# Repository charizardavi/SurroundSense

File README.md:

## SurroundSense by Haptify

Hardware:
- Dual-core XTensa LX7 MCU (ESP32-S3)
- Wifi and BLE capability
- On-board microphone
- Advanced haptic motor driver (DRV2605)

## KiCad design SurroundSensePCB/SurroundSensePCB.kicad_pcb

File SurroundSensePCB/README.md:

## SurroundSense by Haptify

Hardware:
- Dual-core XTensa LX7 MCU (ESP32-S3)
- Wifi and BLE capability
- On-board microphone
- Advanced haptic motor driver (DRV2605)

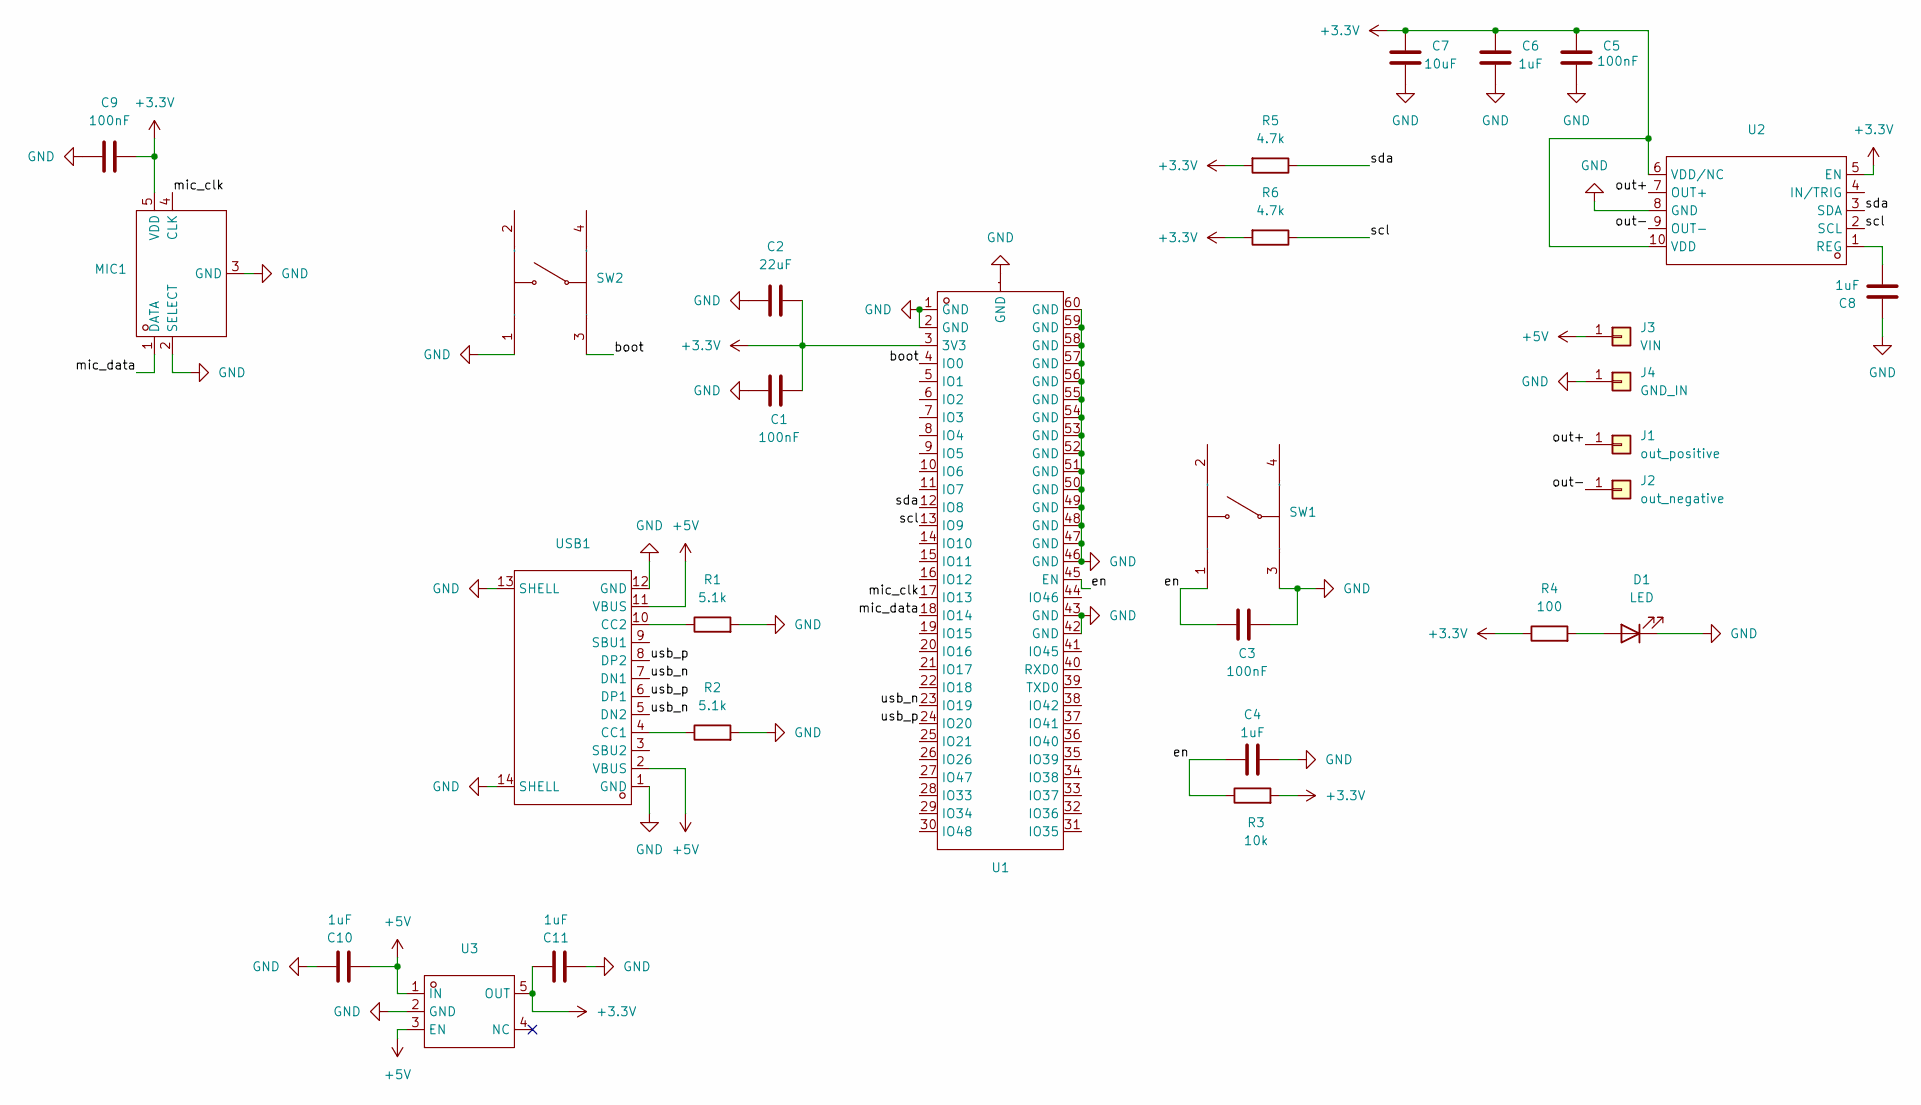
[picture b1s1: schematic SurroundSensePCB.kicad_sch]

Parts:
C1, C3, C5, C9: 100nF; C_0402_1005Metric
C2: 22uF; C_0402_1005Metric
C4, C6, C8, C10, C11: 1uF; C_0402_1005Metric
C7: 10uF; C_0402_1005Metric
D1: LED; LED_0603_1608Metric
J1: out_positive; TestPoint_Pad_D2.0mm
J2: out_negative; TestPoint_Pad_D2.0mm
J3: VIN; TestPoint_Pad_D2.0mm
J4: GND_IN; TestPoint_Pad_D2.0mm
MIC1: MIC-SMD_5P-L3.5-W2.7-TL_MMICT390200012; Manufacturer Part MMICT390200012; LCSC Part Name MMICT390200012
R1, R2: 5.1k; R_0402_1005Metric
R3: 10k; R_0402_1005Metric
R4: 100; R_0402_1005Metric
R5, R6: 4.7k; R_0402_1005Metric
SW1, SW2: SW-SMD_4P-L2.8-W1.9-P1.16-LS3.0; Manufacturer Part TS2819A 230gf; LCSC Part Name 2.8*1.9*0.57mm 立贴 轻触开关
U1: 2.4GHz; BULETM-SMD_ESP32-S3-MINI-1-N8; Manufacturer Part ESP32-S3-MINI-1-N8; LCSC Part Name ESP32-S3-MINI-1-N8
U2: VSSOP-10_L3.0-W3.0-P0.50-LS4.9-BL; Manufacturer Part DRV2605LDGSR; LCSC Part Name 5.5V电机驱动芯片
U3: SOT-23-5_L3.0-W1.7-P0.95-LS2.8-BR; Manufacturer Part TLV75533PDBVR; LCSC Part Name 具有使能功能的 500mA、高 PSRR、低 IQ、低压降稳压器
USB1: USB-C-SMD_TYPE-C-6PIN-2MD-073; Manufacturer Part TYPE-C 16PIN 2MD(073); LCSC Part Name Type-C 母 卧贴

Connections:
+3.3V: C1.1, C2.1, C5.1, C6.1, C7.1, C9.1, C11.1, MIC1.5 (VDD), R3.2, R4.1, R5.2, R6.2, U1.3 (3V3), U2.5 (EN), U2.6 (VDD/NC), U2.10 (VDD), U3.5 (OUT)
+5V: C10.2, J3.1, U3.1 (IN), U3.3 (EN), USB1.2 (VBUS), USB1.11 (VBUS)
/boot: SW2.3 (B), U1.4 (IO0)
/en: C3.2, C4.2, R3.1, SW1.1 (A), U1.45 (EN)
/mic_clk: MIC1.4 (CLK), U1.17 (IO13)
/mic_data: MIC1.1 (DATA), U1.18 (IO14)
/out+: J1.1, U2.7 (OUT+)
/out-: J2.1, U2.9 (OUT-)
/scl: R6.1, U1.13 (IO9), U2.2 (SCL)
/sda: R5.1, U1.12 (IO8), U2.3 (SDA)
/usb_n: U1.23 (IO19), USB1.5 (DN2), USB1.7 (DN1)
/usb_p: U1.24 (IO20), USB1.6 (DP1), USB1.8 (DP2)
GND: C1.2, C2.2, C3.1, C4.1, C5.2, C6.2, C7.2, C8.1, C9.2, C10.1, C11.2, D1.1 (K), J4.1, MIC1.2 (SELECT), MIC1.3 (GND), R1.2, R2.2, SW1.3 (B), SW2.1 (A), U1.1 (GND), U1.2 (GND), U1.42 (GND), U1.43 (GND), U1.46 (GND), U1.47 (GND), U1.48 (GND), U1.49 (GND), U1.50 (GND), U1.51 (GND), U1.52 (GND), U1.53 (GND), U1.54 (GND), U1.55 (GND), U1.56 (GND), U1.57 (GND), U1.58 (GND), U1.59 (GND), U1.60 (GND), U1.GND, U2.8 (GND), U3.2 (GND), USB1.1 (GND), USB1.12 (GND), USB1.13 (SHELL), USB1.14 (SHELL)
unnamed: D1.2 (A), R4.2
unnamed: C8.2, U2.1 (REG)
unnamed: R2.1, USB1.4 (CC1)
unnamed: R1.1, USB1.10 (CC2)

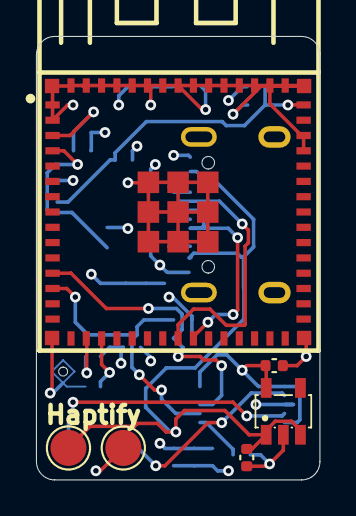
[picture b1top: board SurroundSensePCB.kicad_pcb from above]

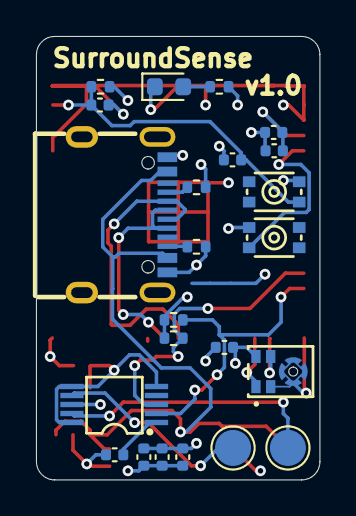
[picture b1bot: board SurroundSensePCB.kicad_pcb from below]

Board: 4 copper layers, 15.7 x 24.6 mm, 29 parts (23 on the bottom side), 17 nets.

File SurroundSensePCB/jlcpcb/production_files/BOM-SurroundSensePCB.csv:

Comment,Designator,Footprint,LCSC
4.7k,"R5,R6",R_0402_1005Metric,C105871
1uF,"C10,C11,C4,C6,C8",C_0402_1005Metric,C14445
100,R4,R_0402_1005Metric,C25076
10k,R3,R_0402_1005Metric,C25744
5.1k,"R1,R2",R_0402_1005Metric,C25905
~,USB1,USB-C-SMD_TYPE-C-6PIN-2MD-073,C2765186
2.4GHz,U1,BULETM-SMD_ESP32-S3-MINI-1-N8,C2913206
~,MIC1,MIC-SMD_5P-L3.5-W2.7-TL_MMICT390200012,C3171752
~,"SW1,SW2",SW-SMD_4P-L2.8-W1.9-P1.16-LS3.0,C388293
~,U3,SOT-23-5_L3.0-W1.7-P0.95-LS2.8-BR,C404027
22uF,C2,C_0402_1005Metric,C415703
~,U2,VSSOP-10_L3.0-W3.0-P0.50-LS4.9-BL,C527464
100nF,"C1,C3,C5,C9",C_0402_1005Metric,C60474
10uF,C7,C_0402_1005Metric,C77000
LED,D1,LED_0603_1608Metric,C965805

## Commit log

2024-12-21 finished BOM, ready for JLC order
2024-12-21 added REAME, added cropped render
2024-12-21 fixed readme (?)
2024-12-21 fixed readme
2024-12-29 parts selected, ordered
